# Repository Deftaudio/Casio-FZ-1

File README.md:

# Hardware upgrades for Casio FZ and VZ series

# FZ-1 / FZ-10m / FZ-20m and VZ-1 / VZ-10m.

This repository is the collection of upgrades for an amazing Casio FZ-series of samplers. Some of those are also applicable for VZ-series. 

- [FZDUMP2026](#fzdump2026) data transfer software for windows

- [1MB FZ-1 Memory Upgrade](#1mb-fz-1-memory-upgrade-board) daughter card memory expansion for FZ-1 

- [Pico OLED Upgrade for FZ-1, FZ-10m, FZ-20m, VZ-1, VZ-10m](#pico-oled-upgrade-for-fz-1-fz-10m-fz-20m-vz-1-vz-10m) easy OLED upgrade for the entire Casio family

- [FZ-1 OLED Upgrade by Dmitrins](#fz-1-oled-upgrade-by-dmitrins) the original design, keep here for historic reason

- [Flashfloppy Floppy Emulator](#flashfloppy-floppy-emulator) configuration files for FlashFloppy and HxC

## FZDUMP2026

It's the new version of the original FZDUMP app for DOS that allowed data transfer between FZ-1 and PC. It has been completely reworked in 2026 (30 years after the original code) to run on "modern" Windows - anything from and including Windows 98 SE.

It was purposely designed to use the parallel port, not rely on any microcontroller, and just initiate a transfer using a user space library to interface with LPT port. This required specific tricks in the code, since the original code used DOS interrupts.
The main motivation is to keep it legacy looking. It has a built in browser to easily manage large sound library. 

FZDUMP2026 remains open source, free of charge of all. You're highly encouraged to submit your improvements using this Github repository. 

Deftaudio offers the complete Thin PC setups with all original and FZDUMP2026 software pre-loaded. Check the [store](https://deftaudio.com/store).  

Below is the [LPT converter](https://github.com/Deftaudio/Casio-FZ-1/tree/main/FZDUMP2026/LPT%20Converter) which is designed to adopt Casio FZ-series pinout and use with standard DB25 Male-Female extension cables to connect to PC. 

LPT converter design files are available to all. You can make your own or order PCB or assembled adapter at Deftaudio [store](https://deftaudio.com/store/tproduct/977905956434-casio-fz-1-lpt-port-adapter).

Developed by Deftaudio.

## 1MB FZ-1 Memory Upgrade board

Memory Expansion is designed to add an extra 1MB of sample memory for Casio FZ-1 (only keyboard version has an expansion slot). It replicates the1987 circuitry by leveraging off the shelf 256Kx1 DRAM chips which are easily obtainable.  

Beginner soldering skills are required. [The kit ](https://github.com/Deftaudio/Casio-FZ-1/blob/main/Memory%20Expansion/Casio%20FZ-1%20Memory%20Expansion%20-%20BOM.pdf)consists of thru hole parts only, easy to solder. It includes quality IC sockets (round pin hole ) for all components for easy installation or replacement. Assembly manual is located [here](https://github.com/Deftaudio/Casio-FZ-1/blob/main/Memory%20Expansion/Casio%20FZ-1%20Memory%20Expansion%20Assembly%20Manual.pdf).

Plug and play. Doesn't require opening FZ-1. The memory expansion slot is located on the back of the instrument.  

Works with any 256Kx1 DRAM (80ns or better) such as MB81256-80, HY53C256LS-80, KM41C256P-7, MN41256A-08 and many other equivalents.

More info on the [Product page](https://deftaudio.com/store/tproduct/857848623614-casio-fz-1-1mb-memory-expansion).

## Pico OLED Upgrade for FZ-1, FZ-10m, FZ-20m, VZ-1, VZ-10m

This is the recent [development by Dreambrother7](https://github.com/Dreambrother7/FZ1oledlc), is inspired by the original OLED by Dmitrins, but uses RPi Pico/Pico2 instead. This allowed to reduce the cost of the project, by minimizing the BOM and using easily available SSD1309 OLED model. 

Deftaudio designed several PCBs for this project. The base PCB assembly hosts Pico and OLED screen. It connects to the adapter board that goes into flex cable slot on Casio. The base PCB has snap off regions to be mounted in FZ-1, FZ-10m/FZ-20m or VZ-10m.  

The adapter board is unique for FZ-1 or FZ-10m/FZ-20m/VZ-10m due to a different connector type which is used on rack family. It connects with 10 pin ribbon cable (2.00mm pitch). 

You can [download](https://github.com/Deftaudio/Casio-FZ-1/tree/main/Pico%20OLED%20by%20Dreambrother7) the lastest PCB design files and Gerber from this repository while Dreambrother7 hosts the latest tested version and [firmware](https://github.com/Dreambrother7/FZ1oledlc/releases).  

You can purchase PCBs at Deftaudio [store](https://deftaudio.com/store).

Developed by Dreambrother7 and Deftaudio.

## FZ-1 OLED Upgrade by Dmitrins

This is a copy of the open source design files by Dmitrins who shared it on [Yamahamusician](https://yamahamusicians.com/forum/viewtopic.php?t=10666&start=240). 

Deftaudio doesn't sell this design. Keep it here just to preserve it.

## Flashfloppy Floppy Emulator

Just a set of configuration files and test images to get Casio FZ-1 running with Flashfloppy.

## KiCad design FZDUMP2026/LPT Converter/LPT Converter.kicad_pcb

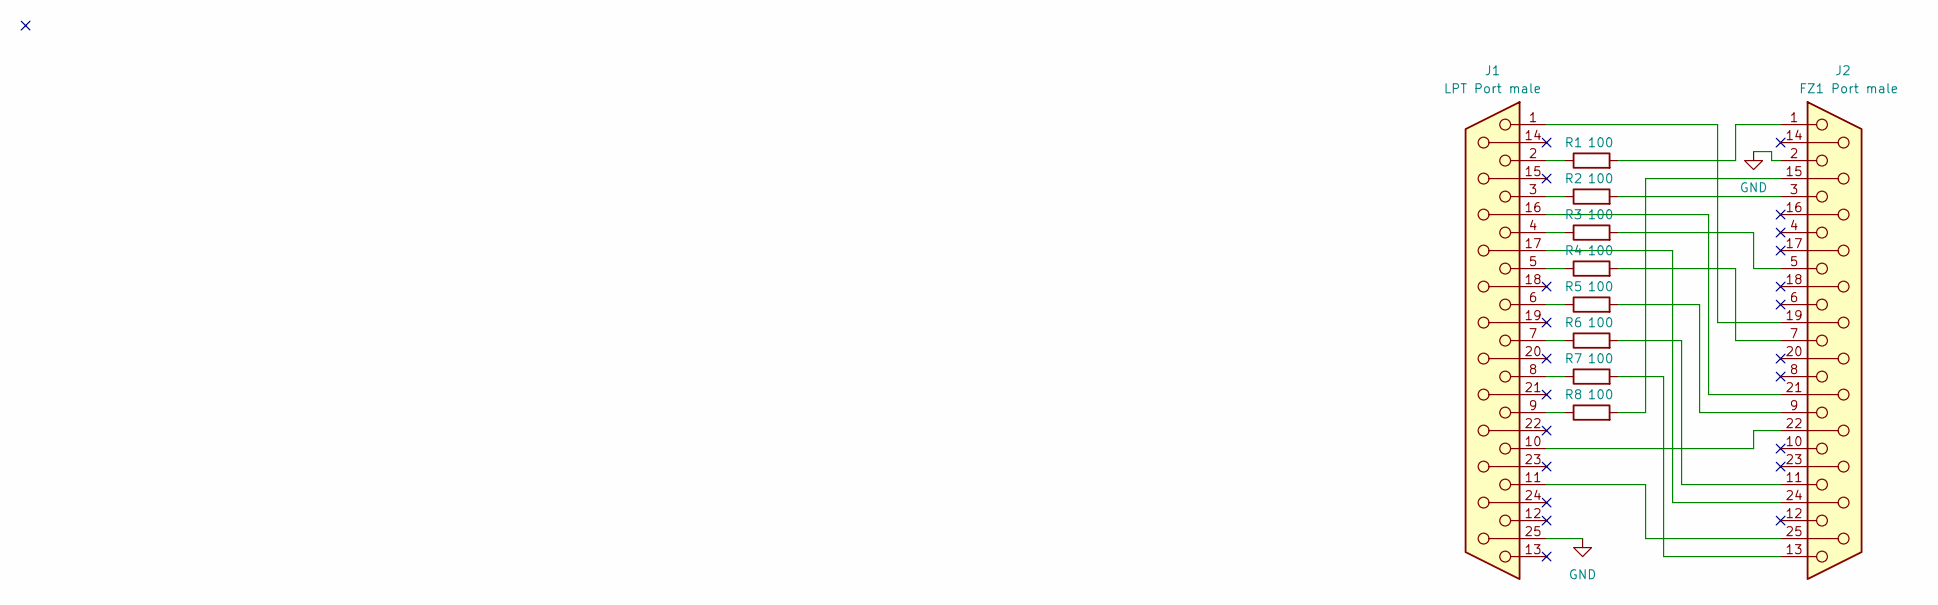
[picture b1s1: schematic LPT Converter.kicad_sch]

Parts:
J1: LPT Port male; DSUB-25_Male_Socket_EdgeMount_P2.77mm
J2: FZ1 Port male; DSUB-25_Male_Socket_EdgeMount_P2.77mm
R1, R2, R3, R4, R5, R6, R7, R8: 100; R_Axial_DIN0207_L6.3mm_D2.5mm_P7.62mm_Horizontal

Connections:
GND: J1.25, J2.2
unnamed: J1.16, J2.21
unnamed: J1.17, J2.24
unnamed: J1.2, R1.1
unnamed: J1.3, R2.1
unnamed: J1.4, R3.1
unnamed: J1.5, R4.1
unnamed: J1.6, R5.1
unnamed: J1.7, R6.1
unnamed: J1.8, R7.1
unnamed: J1.9, R8.1
unnamed: J2.15, R8.2
unnamed: J1.1, J2.19
unnamed: J1.10, J2.22
unnamed: J1.11, J2.25
unnamed: J2.1, R1.2
unnamed: J2.3, R2.2
unnamed: J2.5, R3.2
unnamed: J2.7, R4.2
unnamed: J2.9, R5.2
unnamed: J2.11, R6.2
unnamed: J2.13, R7.2

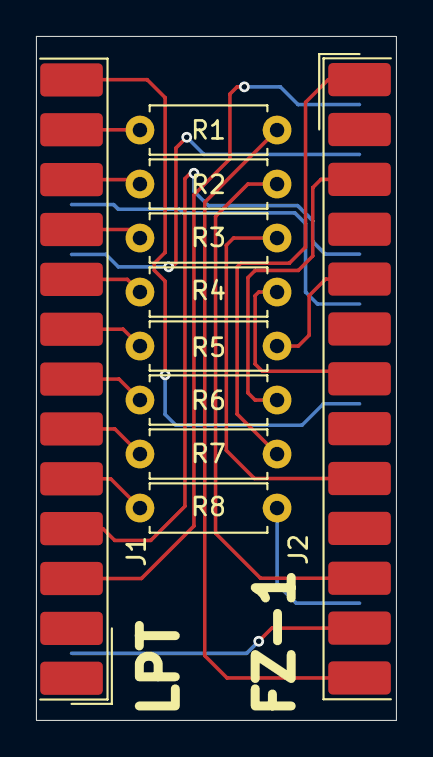
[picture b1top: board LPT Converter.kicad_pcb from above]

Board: 2 copper layers, 20.0 x 38.0 mm, 10 parts (0 on the bottom side), 22 nets.

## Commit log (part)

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2026-04-01 Apply .gitignore to remove macOS junk
2026-05-15 Full doc release
2026-05-15 more info on FZ-1
2026-05-19 Memory Kit updates
2026-06-26 LPT Converter added
2026-06-26 Doc updates
2026-06-28 PICO OLED added
2026-06-28 gerber file updates
2026-06-30 new PCB design updates
